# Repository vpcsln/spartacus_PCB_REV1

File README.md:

# SPARTACUS-HF REV1 PCB

KiCad source of the first assembled board of
[SPARTACUS-HF](https://spartacus-hf.dev), an HF transceiver for amateur and
emergency radio. SPARTACUS-HF is an independent project developed by
Electrical Engineering and Information Technology students at RWTH Aachen
University.

REV1 is assembled in a 3D-printed enclosure. On 2 October 2026 it made its
first two-way FT8 contacts on 40 m (7.074 MHz), handling both receive and
transmit. Calibrated RF, spectral, thermal and protection measurements are
still open.

## The board

| | |
|---|---|
| Size | 175 × 100 mm |
| Layers | 6 layers, 1.6 mm, 35 µm copper; In1 and In4 are ground planes next to the outer layers |
| Parts | 438 footprints, mixed SMD and through-hole, hand-wound RF magnetics |
| Controller | STM32G474; its HRTIM generates the transmit and receive clocks |
| Transmitter | Two Class-D switching branches (BS170) with digital outphasing and envelope control, combined by transformers |
| Receiver | Tayloe quadrature sampling detector with a PCM1821 stereo audio ADC |
| Filters | Five switched low-pass sections with forward/reverse power sensing; receive band-pass filters |
| Interfaces | USB-C power delivery and separate USB-C data, fused barrel input, BNC RF output, three 3.5 mm audio and key ports, SD card, LCD, encoder and buttons |

- [REV1 build and first contacts](https://spartacus-hf.dev/en/rev1-first-contacts/)
- [Interactive board viewer](https://spartacus-hf.dev/en/technology/)
- [S-CTRL](https://github.com/vpcsln/spartacusControl), the Linux desktop and command-line companion

## Open the design

1. Install **KiCad 10.0.5**, including its standard symbol, footprint, and 3D
   model libraries.
2. Clone this repository.
3. Open `v1sch.kicad_pro`.

The custom symbols, footprints, legacy Eagle libraries, and custom 3D models
used by the design are committed below `libraries/`. Both KiCad library tables
use `${KIPRJMOD}` paths, so a clone can live in any directory on Linux, macOS,
or Windows.

## Verify a clone

With KiCad 10.0.5 installed:

```sh
./scripts/verify-project.sh
```

Or use the immutable official KiCad 10.0.4 CLI container:

```sh
make verify-container
```

Reports are written to `build/reports/`. Existing ERC or DRC findings are
reported for engineering review; the verification fails only if the pinned
toolchain is wrong, a required file is missing, a non-portable path is found,
or KiCad cannot load and check the design.

See [REPRODUCIBILITY.md](REPRODUCIBILITY.md) for the reproducibility boundary
and [CONTRIBUTING.md](CONTRIBUTING.md) for the update workflow.

## Licence

The SPARTACUS-HF design files in this repository are licensed under the
[CERN Open Hardware Licence Version 2 - Strongly Reciprocal](LICENSE)
(CERN-OHL-S-2.0). See [NOTICE](NOTICE). The library snapshots under
`libraries/` come from third parties and keep their upstream terms (see
[libraries/README.md](libraries/README.md)).

This is a development design. It has not completed manufacturing, safety,
regulatory, transmitter or receiver qualification.

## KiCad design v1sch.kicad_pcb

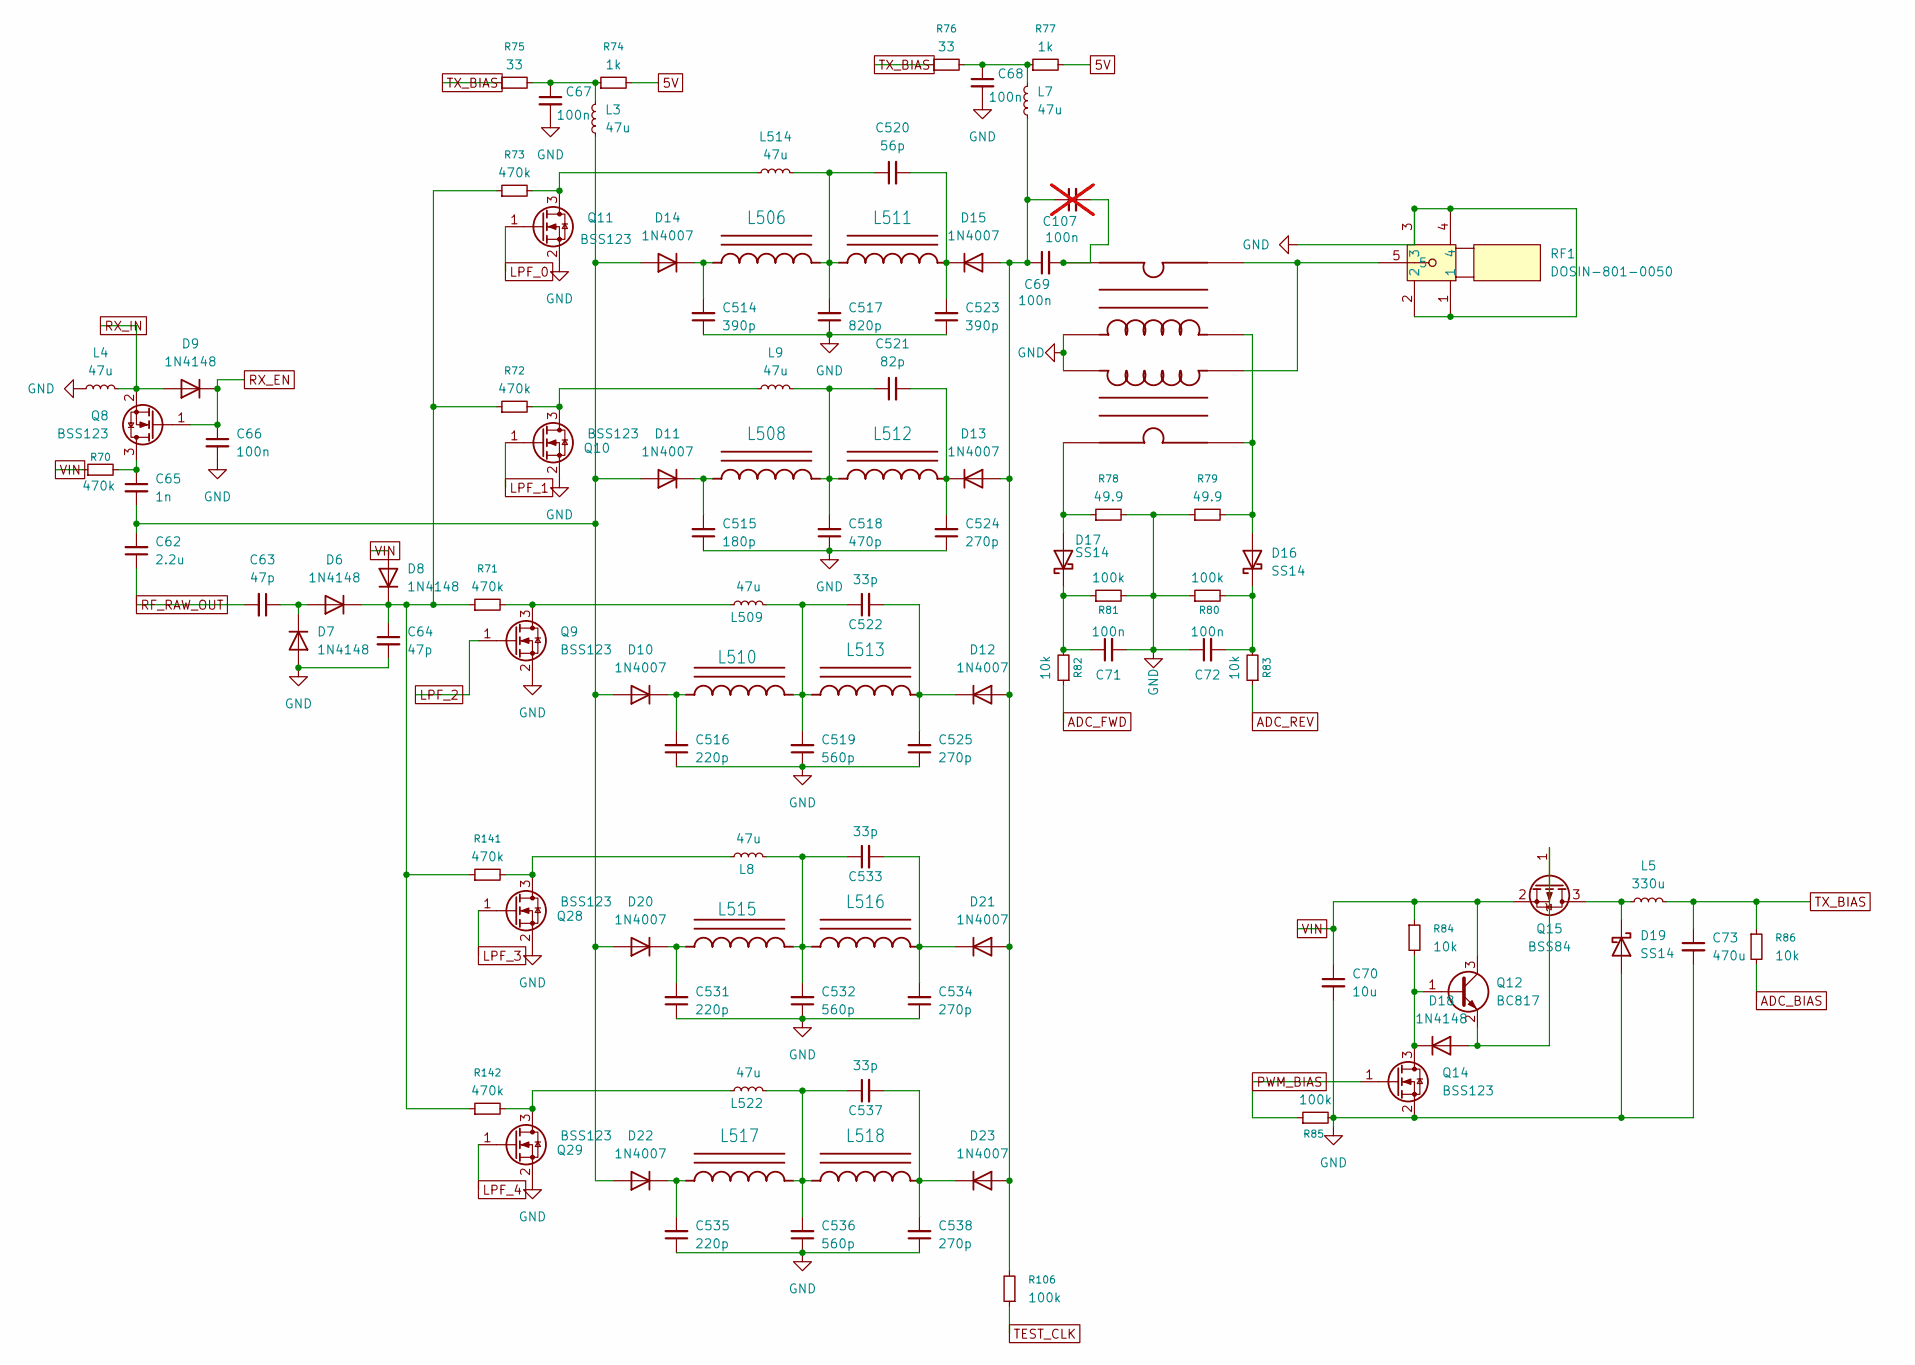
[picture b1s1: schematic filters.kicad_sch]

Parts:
C62: 2.2u; C_1206_3216Metric_Pad1.33x1.80mm_HandSolder
C63, C64: 47p; C_1206_3216Metric_Pad1.33x1.80mm_HandSolder
C65: 1n; C_1206_3216Metric_Pad1.33x1.80mm_HandSolder
C66, C67, C68, C69, C71, C72: 100n; C_1206_3216Metric_Pad1.33x1.80mm_HandSolder
C70: 10u; C_1206_3216Metric_Pad1.33x1.80mm_HandSolder
C73: 470u; CP_Radial_D8.0mm_P3.50mm
C107: 100n; CAP-TH_L4.0-W2.6-P2.5-D0.5; not fitted
C514, C523: 390p; CAP-TH_L4.0-W2.6-P2.5-D0.5
C515: 180p; CAP-TH_L4.0-W2.6-P2.5-D0.5
C516, C531, C535: 220p; CAP-TH_L4.0-W2.6-P2.5-D0.5
C517: 820p; CAP-TH_L4.0-W2.6-P2.5-D0.5
C518: 470p; CAP-TH_L4.0-W2.6-P2.5-D0.5
C519, C532, C536: 560p; CAP-TH_L4.0-W2.6-P2.5-D0.5
C520: 56p; CAP-TH_L4.0-W2.6-P2.5-D0.5
C521: 82p; CAP-TH_L4.0-W2.6-P2.5-D0.5
C522, C533, C537: 33p; CAP-TH_L4.0-W2.6-P2.5-D0.5
C524, C525, C534, C538: 270p; CAP-TH_L4.0-W2.6-P2.5-D0.5
D6, D7, D8, D9, D18: 1N4148; D_DO-35_SOD27_P2.54mm_Vertical_CathodeUp
D10, D11, D12, D13, D14, D15, D20, D21, D22, D23: 1N4007; D_DO-41_SOD81_P3.81mm_Vertical_CathodeUp
D16, D17, D19: SS14; D_SMA
L3, L4, L7, L8, L9, L509, L514, L522: 47u; L_Axial_L9.5mm_D4.0mm_P2.54mm_Vertical_Fastron_SMCC
L5: 330u; L_Axial_L9.5mm_D4.0mm_P2.54mm_Vertical_Fastron_SMCC
L506, L508, L510, L511, L512, L513, L515, L516, L517, L518: T50_INDUCTOR
Q8, Q9, Q10, Q11, Q14, Q28, Q29: BSS123; SOT-23
Q12: BC817; SOT-23
Q15: BSS84; SOT-23
R70, R71, R72, R73, R141, R142: 470k; R_1206_3216Metric_Pad1.30x1.75mm_HandSolder
R74, R77: 1k; R_1206_3216Metric_Pad1.30x1.75mm_HandSolder
R75, R76: 33; R_1206_3216Metric_Pad1.30x1.75mm_HandSolder
R78, R79: 49.9; R_1206_3216Metric_Pad1.30x1.75mm_HandSolder
R80, R81, R85, R106: 100k; R_1206_3216Metric_Pad1.30x1.75mm_HandSolder
R82, R83, R84, R86: 10k; R_1206_3216Metric_Pad1.30x1.75mm_HandSolder
RF1: DOSIN-801-0050; BNC-TH_DOSIN-801-0051; MPN DOSIN-801-0050; LCSC Part C521210
T5: BN43-1502_BRIDGE

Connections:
5V: R74.2, R77.2; also elsewhere on the board
ADC_BIAS: R86.2; also elsewhere on the board
ADC_FWD: R82.1; also elsewhere on the board
ADC_REV: R83.1; also elsewhere on the board
GND: C64.2, C66.2, C67.2, C68.2, C70.2, C71.2, C72.1, C73.2, C514.1, C515.1, C516.1, C517.1, C518.1, C519.1, C523.1, C524.1, C525.1, C531.1, C532.1, C534.1, C535.1, C536.1, C538.1, D7.2 (A), D19.2 (A), L4.1, Q9.2 (S), Q10.2 (S), Q11.2 (S), Q14.2 (S), Q28.2 (S), Q29.2 (S), R78.2, R79.1, R80.1, R81.2, R85.2, RF1.1, RF1.2, RF1.3, RF1.4, T5.C2B, T5.C3B; also elsewhere on the board
LPF_0: Q11.1 (G); also elsewhere on the board
LPF_1: Q10.1 (G); also elsewhere on the board
LPF_2: Q9.1 (G); also elsewhere on the board
LPF_3: Q28.1 (G); also elsewhere on the board
LPF_4: Q29.1 (G); also elsewhere on the board
unnamed: C67.1, L3.2, R74.1, R75.2
unnamed: C68.1, L7.2, R76.2, R77.1
unnamed: C69.2, C107.2, T5.C4B
unnamed: C517.2, C520.1, L506.CA, L511.CB, L514.2
unnamed: C518.2, C521.1, L9.2, L508.CA, L512.CB
unnamed: C519.2, C522.1, L509.2, L510.CA, L513.CB
unnamed: C532.2, C533.1, L8.2, L515.CA, L516.CB
unnamed: C536.2, C537.1, L517.CA, L518.CB, L522.2
unnamed: C63.1, D6.2 (A), D7.1 (K)
unnamed: C64.1, D6.1 (K), D8.1 (K), R71.1, R72.1, R73.1, R141.1, R142.1
unnamed: C62.2, C65.2, D10.2 (A), D11.2 (A), D14.2 (A), D20.2 (A), D22.2 (A), L3.1
unnamed: C516.2, D10.1 (K), L510.CB
unnamed: C515.2, D11.1 (K), L508.CB
unnamed: C69.1, C107.1, D12.2 (A), D13.2 (A), D15.2 (A), D21.2 (A), D23.2 (A), L7.1, R106.2
unnamed: C522.2, C525.2, D12.1 (K), L513.CA
unnamed: C521.2, C524.2, D13.1 (K), L512.CA
unnamed: C514.2, D14.1 (K), L506.CB
unnamed: C520.2, C523.2, D15.1 (K), L511.CA
unnamed: D16.2 (A), R79.2, T5.C1A, T5.C3A
unnamed: C72.2, D16.1 (K), R80.2, R83.2
unnamed: D17.2 (A), R78.1, T5.C1B
unnamed: C71.1, D17.1 (K), R81.1, R82.2
unnamed: D18.2 (A), Q12.2 (E), Q15.1 (G)
unnamed: D18.1 (K), Q12.1 (B), Q14.3 (D), R84.2
unnamed: D19.1 (K), L5.1, Q15.3 (D)
unnamed: C531.2, D20.1 (K), L515.CB
unnamed: C533.2, C534.2, D21.1 (K), L516.CA
unnamed: C535.2, D22.1 (K), L517.CB
unnamed: C537.2, C538.2, D23.1 (K), L518.CA
unnamed: C65.1, Q8.3 (D), R70.2
unnamed: L509.1, Q9.3 (D), R71.2
unnamed: L9.1, Q10.3 (D), R72.2
unnamed: L514.1, Q11.3 (D), R73.2
unnamed: L8.1, Q28.3 (D), R141.2
unnamed: L522.1, Q29.3 (D), R142.2
unnamed: RF1.5, T5.C2A, T5.C4A
PWM_BIAS: Q14.1 (G), R85.1; also elsewhere on the board
RF_RAW_OUT: C62.1, C63.2; also elsewhere on the board
RX_EN: C66.1, D9.1 (K), Q8.1 (G); also elsewhere on the board
RX_IN: D9.2 (A), L4.2, Q8.2 (S); also elsewhere on the board
TEST_CLK: R106.1; also elsewhere on the board
TX_BIAS: C73.1, L5.2, R75.1, R76.1, R86.1
VIN: C70.1, D8.2 (A), Q12.3 (C), Q15.2 (S), R70.1, R84.1; also elsewhere on the board

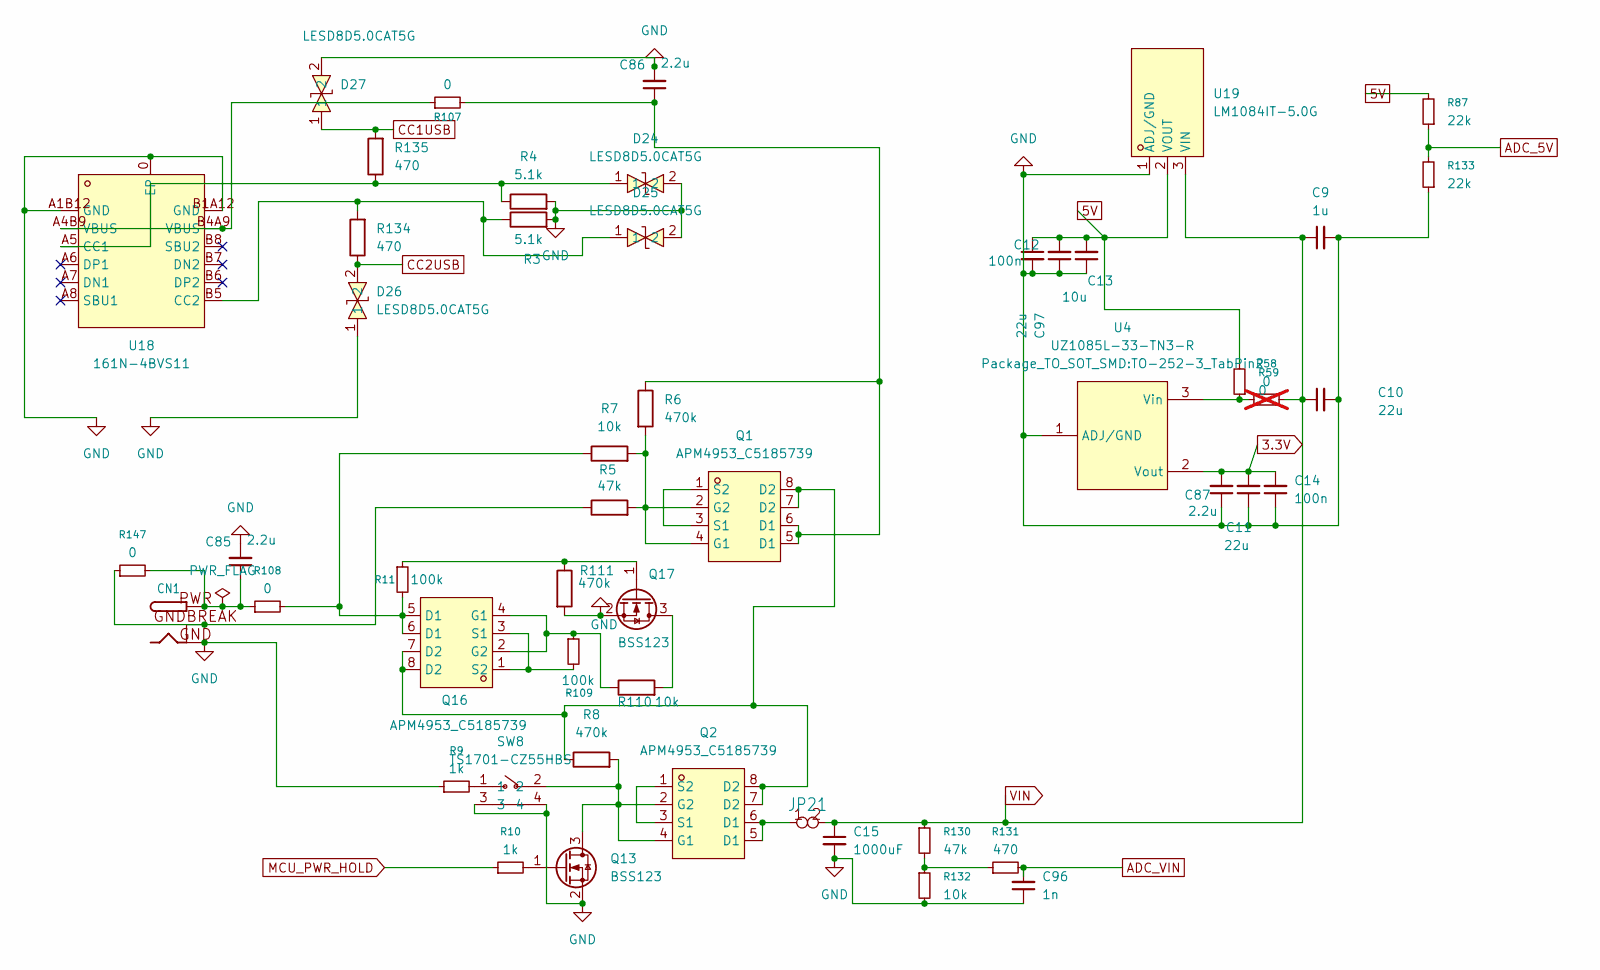
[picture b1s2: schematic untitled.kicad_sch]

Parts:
C9: 1u; C_1206_3216Metric_Pad1.33x1.80mm_HandSolder
C10, C11, C97: 22u; C_1206_3216Metric_Pad1.33x1.80mm_HandSolder
C12, C14: 100n; C_1206_3216Metric_Pad1.33x1.80mm_HandSolder
C13: 10u; C_1206_3216Metric_Pad1.33x1.80mm_HandSolder
C15: 1000uF; CP_Radial_D10.0mm_P5.00mm
C85, C86, C87: 2.2u; C_1206_3216Metric_Pad1.33x1.80mm_HandSolder
C96: 1n; C_1206_3216Metric_Pad1.33x1.80mm_HandSolder
CN1: DCJACK_2MM_PTH
D24, D25, D26, D27: LESD8D5.0CAT5G; D_SOD-882D; MPN LESD8D5.0CAT5G; LCSC Part C172411
JP21: 1X02
Q1, Q2, Q16: APM4953_C5185739; SOP-8_L5.1-W3.9-P1.27-LS6.0-BL; MPN APM4953(UMW); LCSC Part C5185739
Q13, Q17: BSS123; SOT-23
R3, R4: 5.1k; R_1206_3216Metric_Pad1.30x1.75mm_HandSolder
R5, R130: 47k; R_1206_3216Metric_Pad1.30x1.75mm_HandSolder
R6, R8, R111: 470k; R_1206_3216Metric_Pad1.30x1.75mm_HandSolder
R7, R110, R132: 10k; R_1206_3216Metric_Pad1.30x1.75mm_HandSolder
R9, R10: 1k; R_1206_3216Metric_Pad1.30x1.75mm_HandSolder
R11, R109: 100k; R_1206_3216Metric_Pad1.30x1.75mm_HandSolder
R58: 0; R_1206_3216Metric_Pad1.30x1.75mm_HandSolder; not fitted
R59, R107, R108, R147: 0; R_1206_3216Metric_Pad1.30x1.75mm_HandSolder
R87, R133: 22k; R_1206_3216Metric_Pad1.30x1.75mm_HandSolder
R131, R134, R135: 470; R_1206_3216Metric_Pad1.30x1.75mm_HandSolder
SW8: TS1701-CZ55HBS; SW-TH_4P-L7.5-W5.5-P4.50; MPN TS1701-CZ55HBS; LCSC Part C36938820
U4: UZ1085L-33-TN3-R; TO-252-3_TabPin2; MPN UZ1085L-33-TN3-R; LCSC Part C125622
U18: 161N-4BVS11; USB-C-SMD_HANELECTRICITY_161N-4XVS11; MPN 161N-4BVS11; LCSC Part C5440752
U19: LM1084IT-5.0G; TO-220-3_L9.9-W4.5-P2.54-L; MPN LM1084IT-5.0G; LCSC Part C5145342

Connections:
3.3V: C11.2, C14.2, C87.2, U4.2 (Vout); also elsewhere on the board
5V: C12.2, C13.2, C97.1, R59.2, R87.2, U19.2 (VOUT); also elsewhere on the board
ADC_5V: R87.1, R133.2; also elsewhere on the board
ADC_VIN: C96.2, R131.2; also elsewhere on the board
CC1USB: D27.1, R135.2; also elsewhere on the board
CC2USB: D26.2, R134.1; also elsewhere on the board
GND: C9.2, C10.2, C11.1, C12.1, C13.1, C14.1, C15.2, C85.2, C86.2, C87.1, C96.1, C97.2, CN1.GND, D24.2, D25.2, D26.1, D27.2, Q13.2 (S), Q17.2 (S), R3.2, R4.2, R9.1, R111.2, R132.2, R133.1, SW8.3, SW8.4, U4.1 (ADJ/GND), U18.0 (EP), U18.A1B12 (GND), U18.B1A12 (GND), U19.1 (ADJ/GND); also elsewhere on the board
MCU_PWR_HOLD: R10.1; also elsewhere on the board
unnamed: C85.1, CN1.PWR, R108.1, R147.2
unnamed: C86.1, Q1.5 (D1), Q1.6 (D1), R6.1, R107.2
unnamed: CN1.GNDBREAK, R5.1, R147.1
unnamed: JP21.1, Q2.5 (D1), Q2.6 (D1)
unnamed: Q1.7 (D2), Q1.8 (D2), Q2.7 (D2), Q2.8 (D2), Q16.7 (D2), Q16.8 (D2), R8.1
unnamed: Q1.2 (G2), Q1.4 (G1), R5.2, R6.2, R7.2
unnamed: Q1.1 (S2), Q1.3 (S1)
unnamed: Q2.1 (S2), Q2.3 (S1)
unnamed: Q2.2 (G2), Q2.4 (G1), Q13.3 (D), R8.2, SW8.2
unnamed: Q13.1 (G), R10.2
unnamed: Q16.5 (D1), Q16.6 (D1), R7.1, R11.2, R108.2
unnamed: Q16.2 (G2), Q16.4 (G1), R109.1, R110.1
unnamed: Q16.1 (S2), Q16.3 (S1), R109.2
unnamed: Q17.3 (D), R110.2
unnamed: Q17.1 (G), R11.1, R111.1
unnamed: R9.2, SW8.1
unnamed: R107.1, U18.A4B9 (VBUS), U18.B4A9 (VBUS)
unnamed: R130.2, R131.1, R132.1
unnamed: R58.1, R59.1, U4.3 (Vin)
unnamed: D24.1, R4.1, R135.1, U18.A5 (CC1)
unnamed: D25.1, R3.1, R134.2, U18.B5 (CC2)
VIN: C9.1, C10.1, C15.1, JP21.2, R58.2, R130.1, U19.3 (VIN); also elsewhere on the board

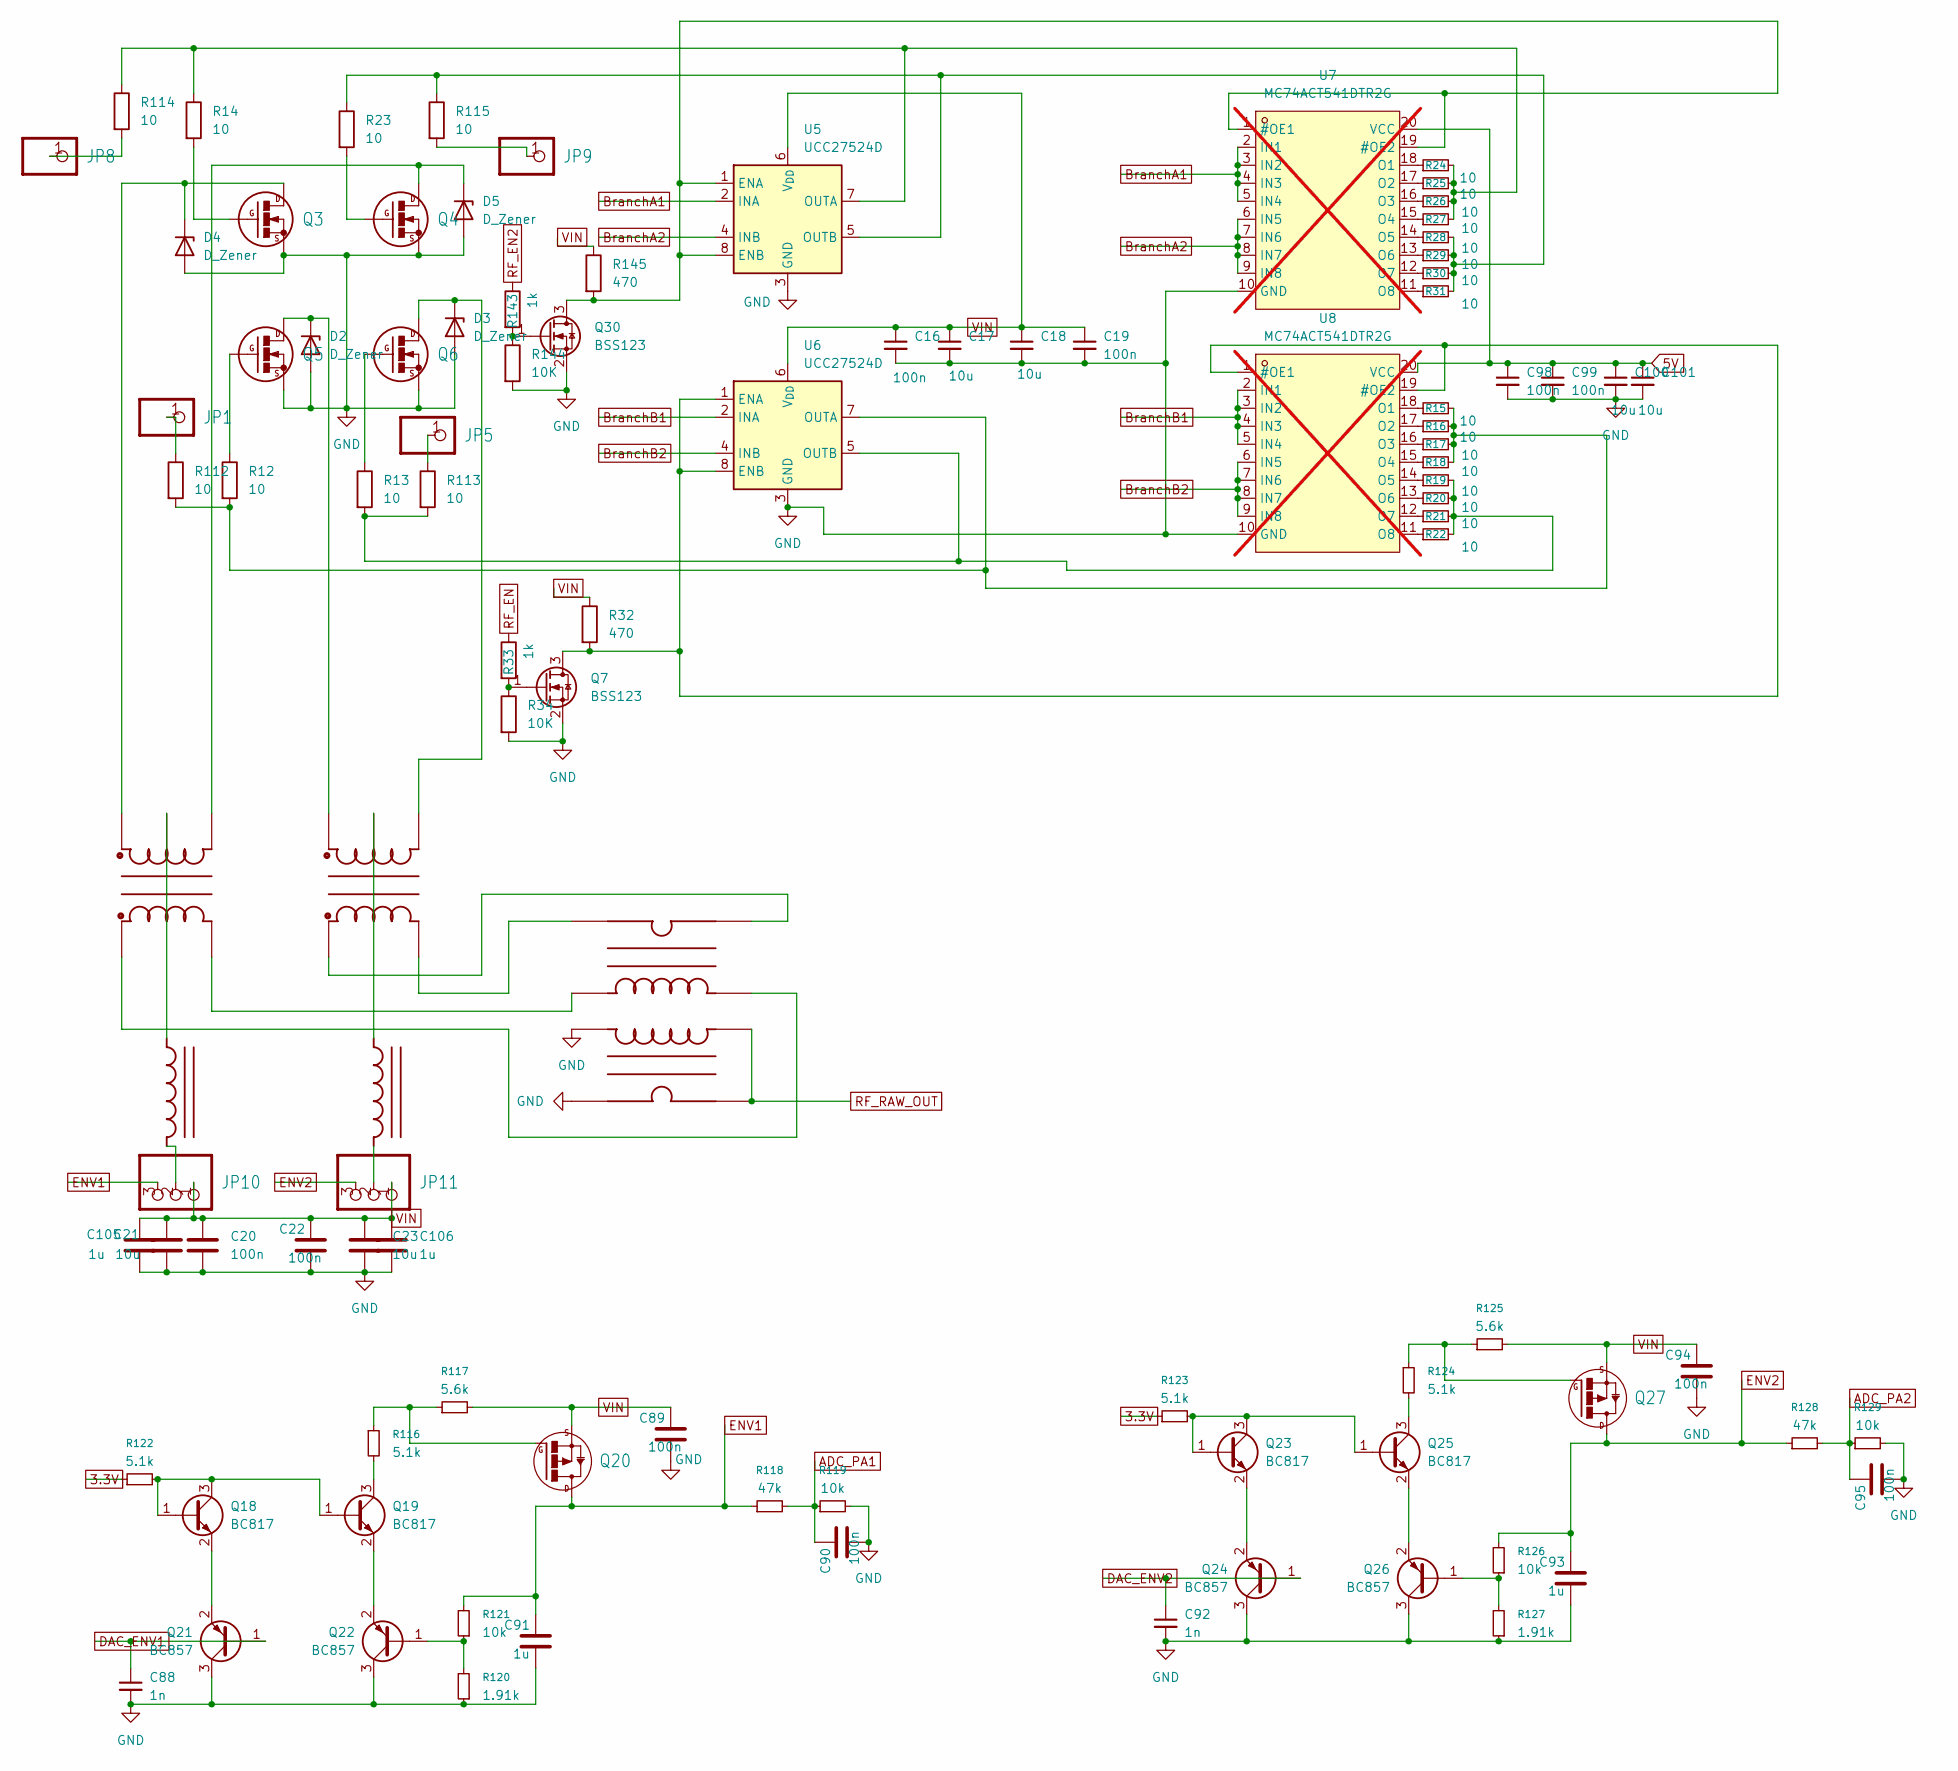
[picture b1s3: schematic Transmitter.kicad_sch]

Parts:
C16, C19, C20, C22, C89, C90, C94, C95, C98, C99: 100n; C_1206_3216Metric_Pad1.33x1.80mm_HandSolder
C17, C18, C21, C23, C100, C101: 10u; C_1206_3216Metric_Pad1.33x1.80mm_HandSolder
C88, C92: 1n; C_1206_3216Metric_Pad1.33x1.80mm_HandSolder
C91, C93, C105, C106: 1u; C_1206_3216Metric_Pad1.33x1.80mm_HandSolder
D2, D3, D4, D5: D_Zener; D_DO-41_SOD81_P3.81mm_Vertical_CathodeUp
JP1, JP5, JP8, JP9: 1X01
JP10, JP11: 1X03
L1, L2: T37_INDUCTOR
Q3, Q4, Q5, Q6: SOT54E_LYING_100_LH2
Q7, Q30: BSS123; SOT-23
Q18, Q19, Q23, Q25: BC817; SOT-23
Q20, Q27: DPAK4
Q21, Q22, Q24, Q26: BC857; SOT-23
R12, R13, R14, R15, R16, R17, R18, R19, R20, R21, R22, R23, R24, R25, R26, R27, R28, R29, R30, R31, R112, R113, R114, R115: 10; R_1206_3216Metric_Pad1.30x1.75mm_HandSolder
R32, R145: 470; R_1206_3216Metric_Pad1.30x1.75mm_HandSolder
R33, R143: 1k; R_1206_3216Metric_Pad1.30x1.75mm_HandSolder
R34, R144: 10K; R_1206_3216Metric_Pad1.30x1.75mm_HandSolder
R116, R122, R123, R124: 5.1k; R_1206_3216Metric_Pad1.30x1.75mm_HandSolder
R117, R125: 5.6k; R_1206_3216Metric_Pad1.30x1.75mm_HandSolder
R118, R128: 47k; R_1206_3216Metric_Pad1.30x1.75mm_HandSolder
R119, R121, R126, R129: 10k; R_1206_3216Metric_Pad1.30x1.75mm_HandSolder
R120, R127: 1.91k; R_1206_3216Metric_Pad1.30x1.75mm_HandSolder
T1, T2: BN43-202-TAP
T3: BN43-202_BRIDGE
U5, U6: UCC27524D; SOIC-8_3.9x4.9mm_P1.27mm
U7, U8: MC74ACT541DTR2G; TSSOP-20_L6.5-W4.4-P0.65-LS6.4-BL; MPN MC74ACT541DTR2G; LCSC Part C8112; not fitted

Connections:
3.3V: R122.1, R123.1; also elsewhere on the board
5V: C98.1, C99.1, C100.1, C101.1, U7.20 (VCC), U8.20 (VCC); also elsewhere on the board
ADC_PA1: C90.1, R118.2, R119.1; also elsewhere on the board
ADC_PA2: C95.1, R128.2, R129.1; also elsewhere on the board
BranchA1: U5.2 (INA), U7.2 (IN1), U7.3 (IN2), U7.4 (IN3), U7.5 (IN4); also elsewhere on the board
BranchA2: U5.4 (INB), U7.6 (IN5), U7.7 (IN6), U7.8 (IN7), U7.9 (IN8); also elsewhere on the board
BranchB1: U6.2 (INA), U8.2 (IN1), U8.3 (IN2), U8.4 (IN3), U8.5 (IN4); also elsewhere on the board
BranchB2: U6.4 (INB), U8.6 (IN5), U8.7 (IN6), U8.8 (IN7), U8.9 (IN8); also elsewhere on the board
DAC_ENV1: C88.1, Q21.1 (B); also elsewhere on the board
DAC_ENV2: C92.1, Q24.1 (B); also elsewhere on the board
ENV1: C91.1, JP10.3, Q20.4 (D), R118.1, R121.2
ENV2: C93.1, JP11.3, Q27.4 (D), R126.2, R128.1
GND: C16.2, C17.2, C18.2, C19.2, C20.2, C21.2, C22.2, C23.2, C88.2, C89.2, C90.2, C91.2, C92.2, C93.2, C94.2, C95.2, C98.2, C99.2, C100.2, C101.2, C105.2, C106.2, D2.2 (A), D3.2 (A), D4.2 (A), D5.2 (A), Q3.S, Q4.S, Q5.S, Q6.S, Q7.2 (S), Q21.3 (C), Q22.3 (C), Q24.3 (C), Q26.3 (C), Q30.2 (S), R34.2, R119.2, R120.1, R127.1, R129.2, R144.2, T3.C1B, T3.C2B, U5.3 (GND), U6.3 (GND), U7.10 (GND), U8.10 (GND); also elsewhere on the board
unnamed: D2.1 (K), Q5.D, T2.C2B
unnamed: D3.1 (K), Q6.D, T2.C2A
unnamed: D4.1 (K), Q3.D, T1.C2B
unnamed: D5.1 (K), Q4.D, T1.C2A
unnamed: JP1.1 (1_1), R112.1
unnamed: JP5.1 (1_1), R113.1
unnamed: JP8.1 (1_1), R114.2
unnamed: JP9.1 (1_1), R115.2
unnamed: JP10.2, L1.CA
unnamed: JP11.2, L2.CA
unnamed: L1.CB, T1.C2C
unnamed: L2.CB, T2.C2C
unnamed: Q3.G, R14.2
unnamed: Q4.G, R23.2
unnamed: Q5.G, R12.1
unnamed: Q6.G, R13.1
unnamed: Q7.3 (D), R32.2, U6.1 (ENA), U6.8 (ENB), U8.1 (#OE1), U8.19 (#OE2)
unnamed: Q7.1 (G), R33.2, R34.1
unnamed: Q18.1 (B), Q18.3 (C), Q19.1 (B), R122.2
unnamed: Q18.2 (E), Q21.2 (E)
unnamed: Q19.3 (C), R116.2
unnamed: Q19.2 (E), Q22.2 (E)
unnamed: Q20.1 (G), R116.1, R117.1
unnamed: Q22.1 (B), R120.2, R121.1
unnamed: Q23.1 (B), Q23.3 (C), Q25.1 (B), R123.2
unnamed: Q23.2 (E), Q24.2 (E)
unnamed: Q25.3 (C), R124.2
unnamed: Q25.2 (E), Q26.2 (E)
unnamed: Q26.1 (B), R126.1, R127.2
unnamed: Q27.1 (G), R124.1, R125.1
unnamed: Q30.3 (D), R145.2, U5.1 (ENA), U5.8 (ENB), U7.1 (#OE1), U7.19 (#OE2)
unnamed: Q30.1 (G), R143.2, R144.1
unnamed: T1.C1A, T3.C3B
unnamed: T1.C1B, T3.C3A
unnamed: T2.C1A, T3.C4B
unnamed: T2.C1B, T3.C4A
unnamed: R14.1, R24.2, R25.2, R26.2, R27.2, R114.1, U5.7 (OUTA)
unnamed: R23.1, R28.2, R29.2, R30.2, R31.2, R115.1, U5.5 (OUTB)
unnamed: R12.2, R15.2, R16.2, R17.2, R18.2, R112.2, U6.7 (OUTA)
unnamed: R13.2, R19.2, R20.2, R21.2, R22.2, R113.2, U6.5 (OUTB)
unnamed: R24.1, U7.18 (O1)
unnamed: R25.1, U7.17 (O2)
unnamed: R26.1, U7.16 (O3)
unnamed: R27.1, U7.15 (O4)
unnamed: R28.1, U7.14 (O5)
unnamed: R29.1, U7.13 (O6)
unnamed: R30.1, U7.12 (O7)
unnamed: R31.1, U7.11 (O8)
unnamed: R15.1, U8.18 (O1)
unnamed: R16.1, U8.17 (O2)
unnamed: R17.1, U8.16 (O3)
unnamed: R18.1, U8.15 (O4)
unnamed: R19.1, U8.14 (O5)
unnamed: R20.1, U8.13 (O6)
unnamed: R21.1, U8.12 (O7)
unnamed: R22.1, U8.11 (O8)
RF_EN: R33.1; also elsewhere on the board
RF_EN2: R143.1; also elsewhere on the board
RF_RAW_OUT: T3.C1A, T3.C2A; also elsewhere on the board
VIN: C16.1, C17.1, C18.1, C19.1, C20.1, C21.1, C22.1, C23.1, C89.1, C94.1, C105.1, C106.1, JP10.1, JP11.1, Q20.3 (S), Q27.3 (S), R32.1, R117.2, R125.2, R145.1, U5.6 (V_{DD}), U6.6 (V_{DD}); also elsewhere on the board

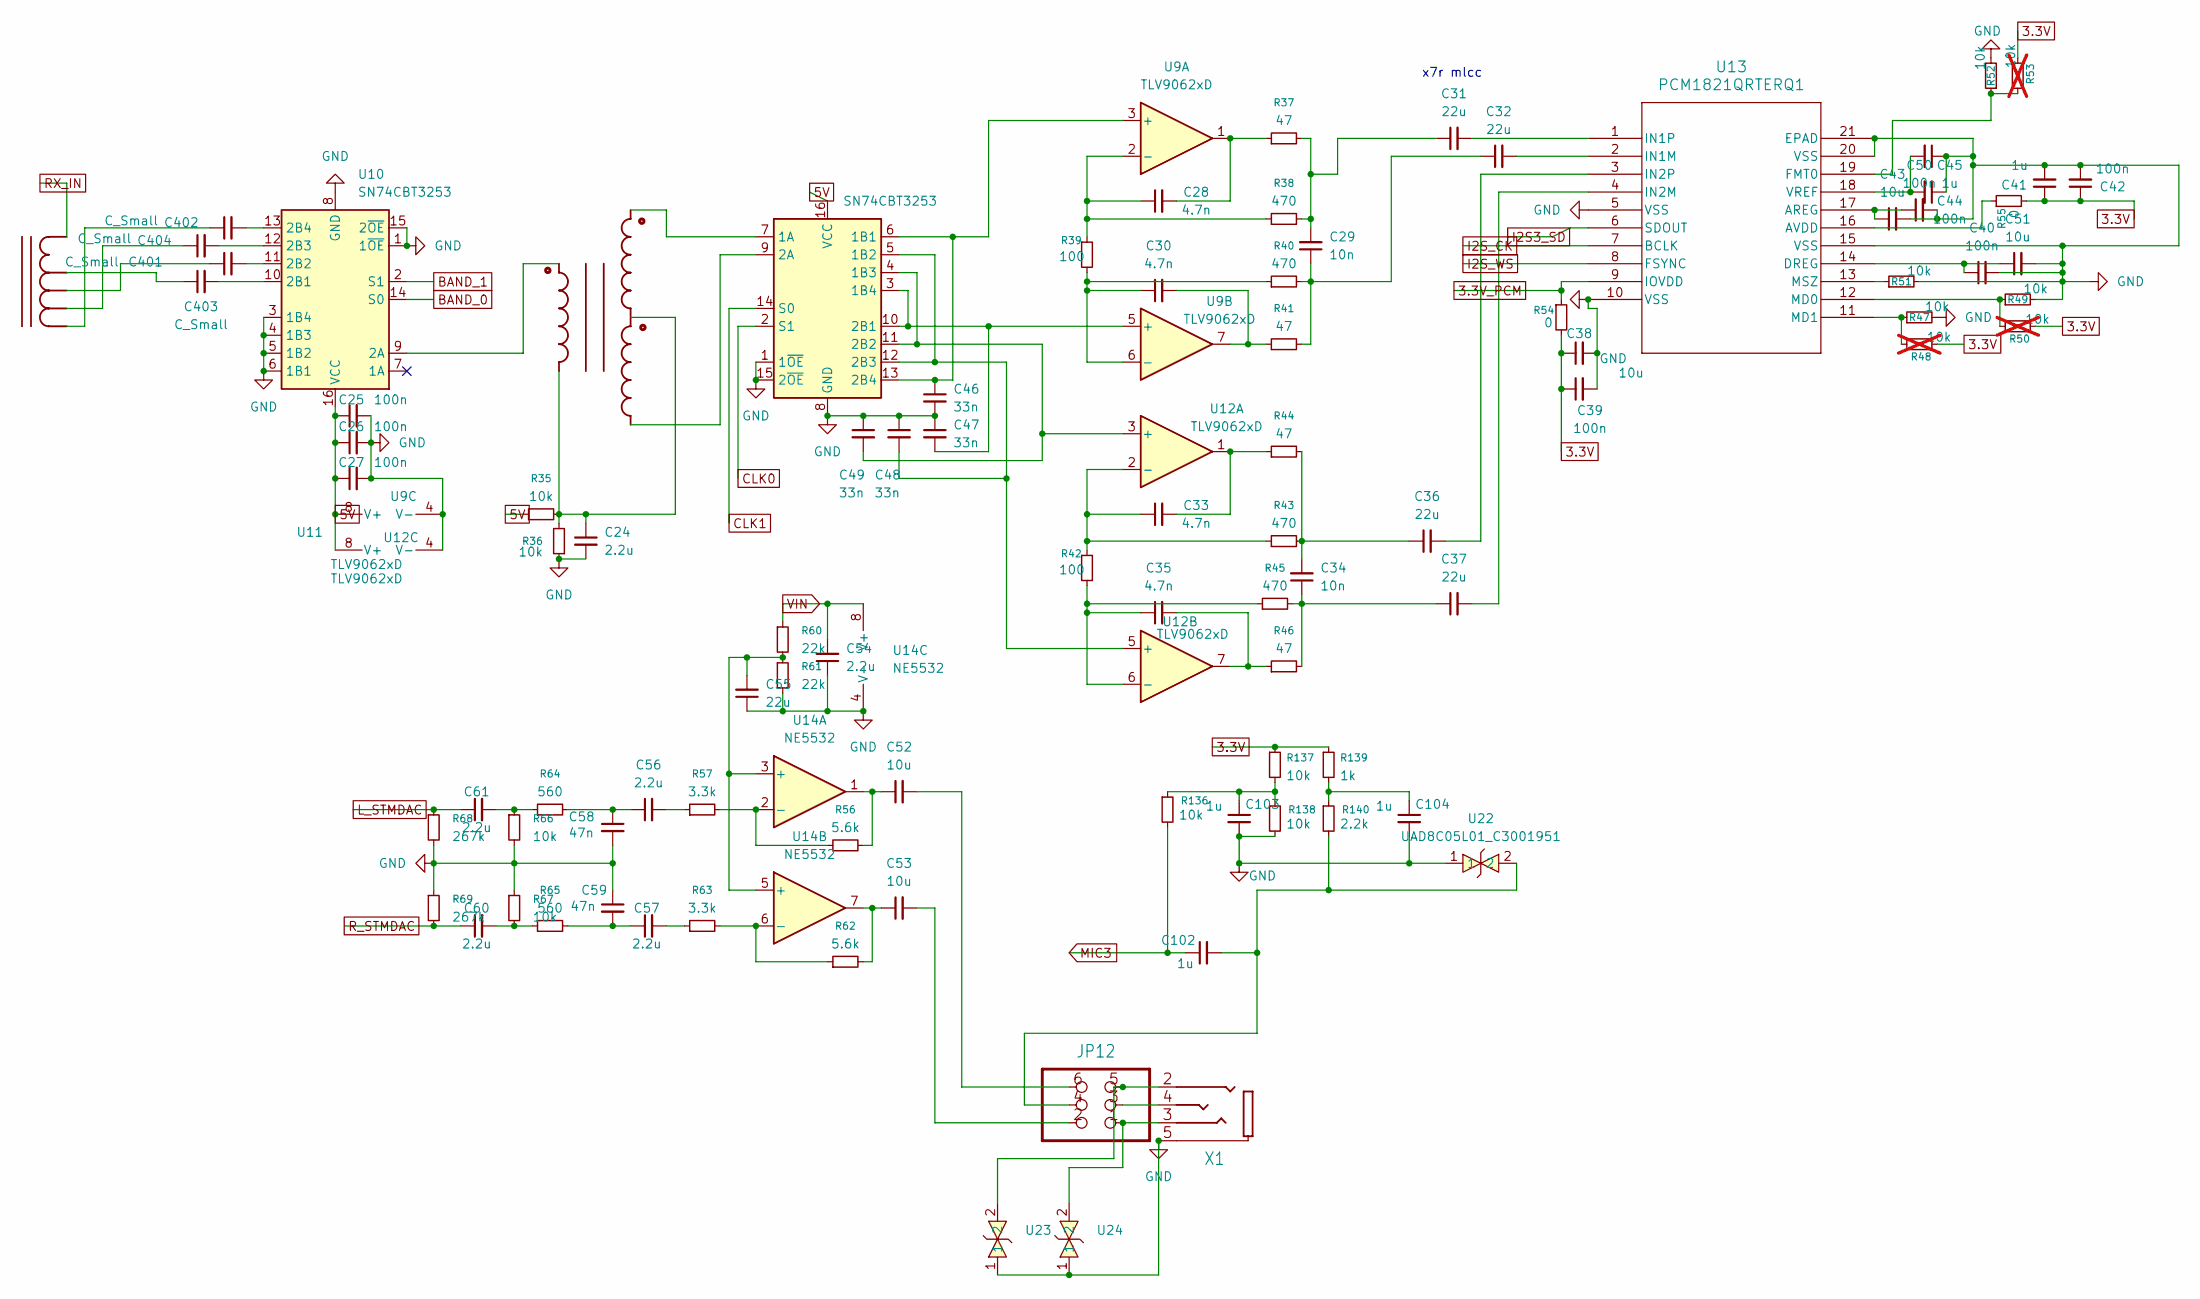
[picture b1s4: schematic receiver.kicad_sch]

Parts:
C24, C54, C56, C57, C60, C61: 2.2u; C_1206_3216Metric_Pad1.33x1.80mm_HandSolder
C25, C26, C27, C39, C40, C42, C44, C50: 100n; C_1206_3216Metric_Pad1.33x1.80mm_HandSolder
C28, C30, C33, C35: 4.7n; C_1206_3216Metric_Pad1.33x1.80mm_HandSolder
C29, C34: 10n; C_1206_3216Metric_Pad1.33x1.80mm_HandSolder
C31, C32, C36, C37, C55: 22u; C_1206_3216Metric_Pad1.33x1.80mm_HandSolder
C38, C43, C51, C52, C53: 10u; C_1206_3216Metric_Pad1.33x1.80mm_HandSolder
C41, C45, C102, C103, C104: 1u; C_1206_3216Metric_Pad1.33x1.80mm_HandSolder
C46, C47, C48, C49: 33n; C_1206_3216Metric_Pad1.33x1.80mm_HandSolder
C58, C59: 47n; C_1206_3216Metric_Pad1.33x1.80mm_HandSolder
C401, C402, C403, C404: C_Small; CAP-TH_L4.0-W2.6-P2.5-D0.5
JP12: 2X03
L401: T50_TAPPED_INDUCTOR_FLAT
R35, R36, R47, R49, R51, R52, R66, R67, R136, R137, R138: 10k; R_1206_3216Metric_Pad1.30x1.75mm_HandSolder
R37, R41, R44, R46: 47; R_1206_3216Metric_Pad1.30x1.75mm_HandSolder
R38, R40, R43, R45: 470; R_1206_3216Metric_Pad1.30x1.75mm_HandSolder
R39, R42: 100; R_1206_3216Metric_Pad1.30x1.75mm_HandSolder
R48, R50, R53: 10k; R_1206_3216Metric_Pad1.30x1.75mm_HandSolder; not fitted
R54, R55: 0; R_1206_3216Metric_Pad1.30x1.75mm_HandSolder
R56, R62: 5.6k; R_1206_3216Metric_Pad1.30x1.75mm_HandSolder
R57, R63: 3.3k; R_1206_3216Metric_Pad1.30x1.75mm_HandSolder
R60, R61: 22k; R_1206_3216Metric_Pad1.30x1.75mm_HandSolder
R64, R65: 560; R_1206_3216Metric_Pad1.30x1.75mm_HandSolder
R68, R69: 267k; R_1206_3216Metric_Pad1.30x1.75mm_HandSolder
R139: 1k; R_1206_3216Metric_Pad1.30x1.75mm_HandSolder
R140: 2.2k; R_1206_3216Metric_Pad1.30x1.75mm_HandSolder
T401: T37_TRIFILAR_TRANSFORMER
U9, U12: TLV9062xD; SOIC-8_3.9x4.9mm_P1.27mm
U10, U11: SN74CBT3253; SOIC-16_3.9x9.9mm_P1.27mm
U13: PCM1821QRTERQ1; WQFN20_RTE_TEX
U14: NE5532; SOIC-8_3.9x4.9mm_P1.27mm
U22, U23, U24: UAD8C05L01_C3001951; SOD-882_L1.0-W0.6-BI; MPN UAD8C05L01(UMW); LCSC Part C3001951
X1: PJ320A

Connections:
3.3V: C38.1, C39.1, C41.1, C42.1, R48.2, R50.2, R53.2, R54.2, R55.2, R137.1, R139.1; also elsewhere on the board
3.3V_PCM: R54.1, U13.9 (IOVDD)
5V: C25.1, C26.1, C27.1, R35.1, U9.8 (V+), U10.16 (VCC), U11.16 (VCC), U12.8 (V+); also elsewhere on the board
BAND_0: U10.14 (S0); also elsewhere on the board
BAND_1: U10.2 (S1); also elsewhere on the board
CLK0: U11.2 (S1); also elsewhere on the board
CLK1: U11.14 (S0); also elsewhere on the board
GND: C24.2, C25.2, C26.2, C27.2, C38.2, C39.2, C40.2, C41.2, C42.2, C43.2, C44.1, C45.1, C46.2, C47.1, C48.1, C49.1, C50.2, C51.2, C54.1, C55.1, C58.2, C59.1, C103.2, C104.2, R36.1, R47.2, R49.2, R51.2, R52.2, R61.2, R66.2, R67.1, R68.2, R69.1, R138.2, U9.4 (V-), U10.1 (1~OE), U10.3 (1B4), U10.4 (1B3), U10.5 (1B2), U10.6 (1B1), U10.8 (GND), U10.15 (2~OE), U11.1 (1~OE), U11.8 (GND), U11.15 (2~OE), U12.4 (V-), U13.5 (VSS), U13.10 (VSS), U13.15 (VSS), U13.20 (VSS), U13.21 (EPAD), U14.4 (V-), U22.1, U23.1, U24.1, X1.5; also elsewhere on the board
I2S3_SD: U13.6 (SDOUT); also elsewhere on the board
I2S_CK: U13.7 (BCLK); also elsewhere on the board
I2S_WS: U13.8 (FSYNC); also elsewhere on the board
L_STMDAC: C61.1, R68.1; also elsewhere on the board
MIC3: C102.1, R136.2; also elsewhere on the board
unnamed: C24.1, R35.2, R36.2, T401.C1A, T401.C2A, T401.C3B
unnamed: C28.2, R37.1, U9.1
unnamed: C29.1, C32.1, R40.2, R41.2
unnamed: C29.2, C31.1, R37.2, R38.2
unnamed: C30.2, R41.1, U9.7
unnamed: C33.2, R44.1, U12.1
unnamed: C34.1, C37.1, R45.2, R46.2
unnamed: C34.2, C36.1, R43.2, R44.2
unnamed: C35.2, R46.1, U12.7
unnamed: C52.1, R56.2, U14.1
unnamed: C52.2, JP12.6
unnamed: C53.1, R62.2, U14.7
unnamed: C53.2, JP12.2
unnamed: C56.1, C58.1, R64.2
unnamed: C56.2, R57.1
unnamed: C57.1, C59.2, R65.2
unnamed: C57.2, R63.1
unnamed: C60.2, R65.1, R67.2
unnamed: C61.2, R64.1, R66.1
unnamed: C102.2, JP12.4, R140.2, U22.2
unnamed: C103.1, R136.1, R137.2, R138.1
unnamed: C104.1, R139.2, R140.1
unnamed: JP12.1, U24.2, X1.3
unnamed: JP12.3, X1.4
unnamed: JP12.5, U23.2, X1.2
unnamed: C403.1, L401.C1B (CB)
unnamed: C401.1, L401.C1C (CC)
unnamed: C404.1, L401.C1D (CD)
unnamed: C402.1, L401.C1E (CE)
unnamed: C28.1, R38.1, R39.1, U9.2 (-)
unnamed: C30.1, R39.2, R40.1, U9.6 (-)
unnamed: T401.C1B, U10.9 (2A)
unnamed: C403.2, U10.10 (2B1)
unnamed: C401.2, U10.11 (2B2)
unnamed: C404.2, U10.12 (2B3)
unnamed: C402.2, U10.13 (2B4)
unnamed: T401.C2B, U11.7 (1A)
unnamed: C46.1, U9.3 (+), U11.6 (1B1), U11.13 (2B4)
unnamed: C48.2, U11.5 (1B2), U11.12 (2B3), U12.5 (+)
unnamed: C49.2, U11.4 (1B3), U11.11 (2B2), U12.3 (+)
unnamed: C47.2, U9.5 (+), U11.3 (1B4), U11.10 (2B1)
unnamed: T401.C3A, U11.9 (2A)
unnamed: C33.1, R42.1, R43.1, U12.2 (-)
unnamed: C35.1, R42.2, R45.1, U12.6 (-)
unnamed: C43.1, C50.1, U13.17 (AREG)
unnamed: R55.1, U13.16 (AVDD)
unnamed: C40.1, C51.1, U13.14 (DREG)
unnamed: R52.1, R53.1, U13.19 (FMT0)
unnamed: C32.2, U13.2 (IN1M)
unnamed: C31.2, U13.1 (IN1P)
unnamed: C37.2, U13.4 (IN2M)
unnamed: C36.2, U13.3 (IN2P)
unnamed: R49.1, R50.1, U13.12 (MD0)
unnamed: R47.1, R48.1, U13.11 (MD1)
unnamed: R51.1, U13.13 (MSZ)
unnamed: C44.2, C45.2, U13.18 (VREF)
unnamed: C55.2, R60.2, R61.1, U14.3 (+), U14.5 (+)
unnamed: R56.1, R57.2, U14.2 (-)
unnamed: R62.1, R63.2, U14.6 (-)
RX_IN: L401.C1A (CA); also elsewhere on the board
R_STMDAC: C60.1, R69.2; also elsewhere on the board
VIN: C54.2, R60.1, U14.8 (V+); also elsewhere on the board

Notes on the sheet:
x7r mlcc
